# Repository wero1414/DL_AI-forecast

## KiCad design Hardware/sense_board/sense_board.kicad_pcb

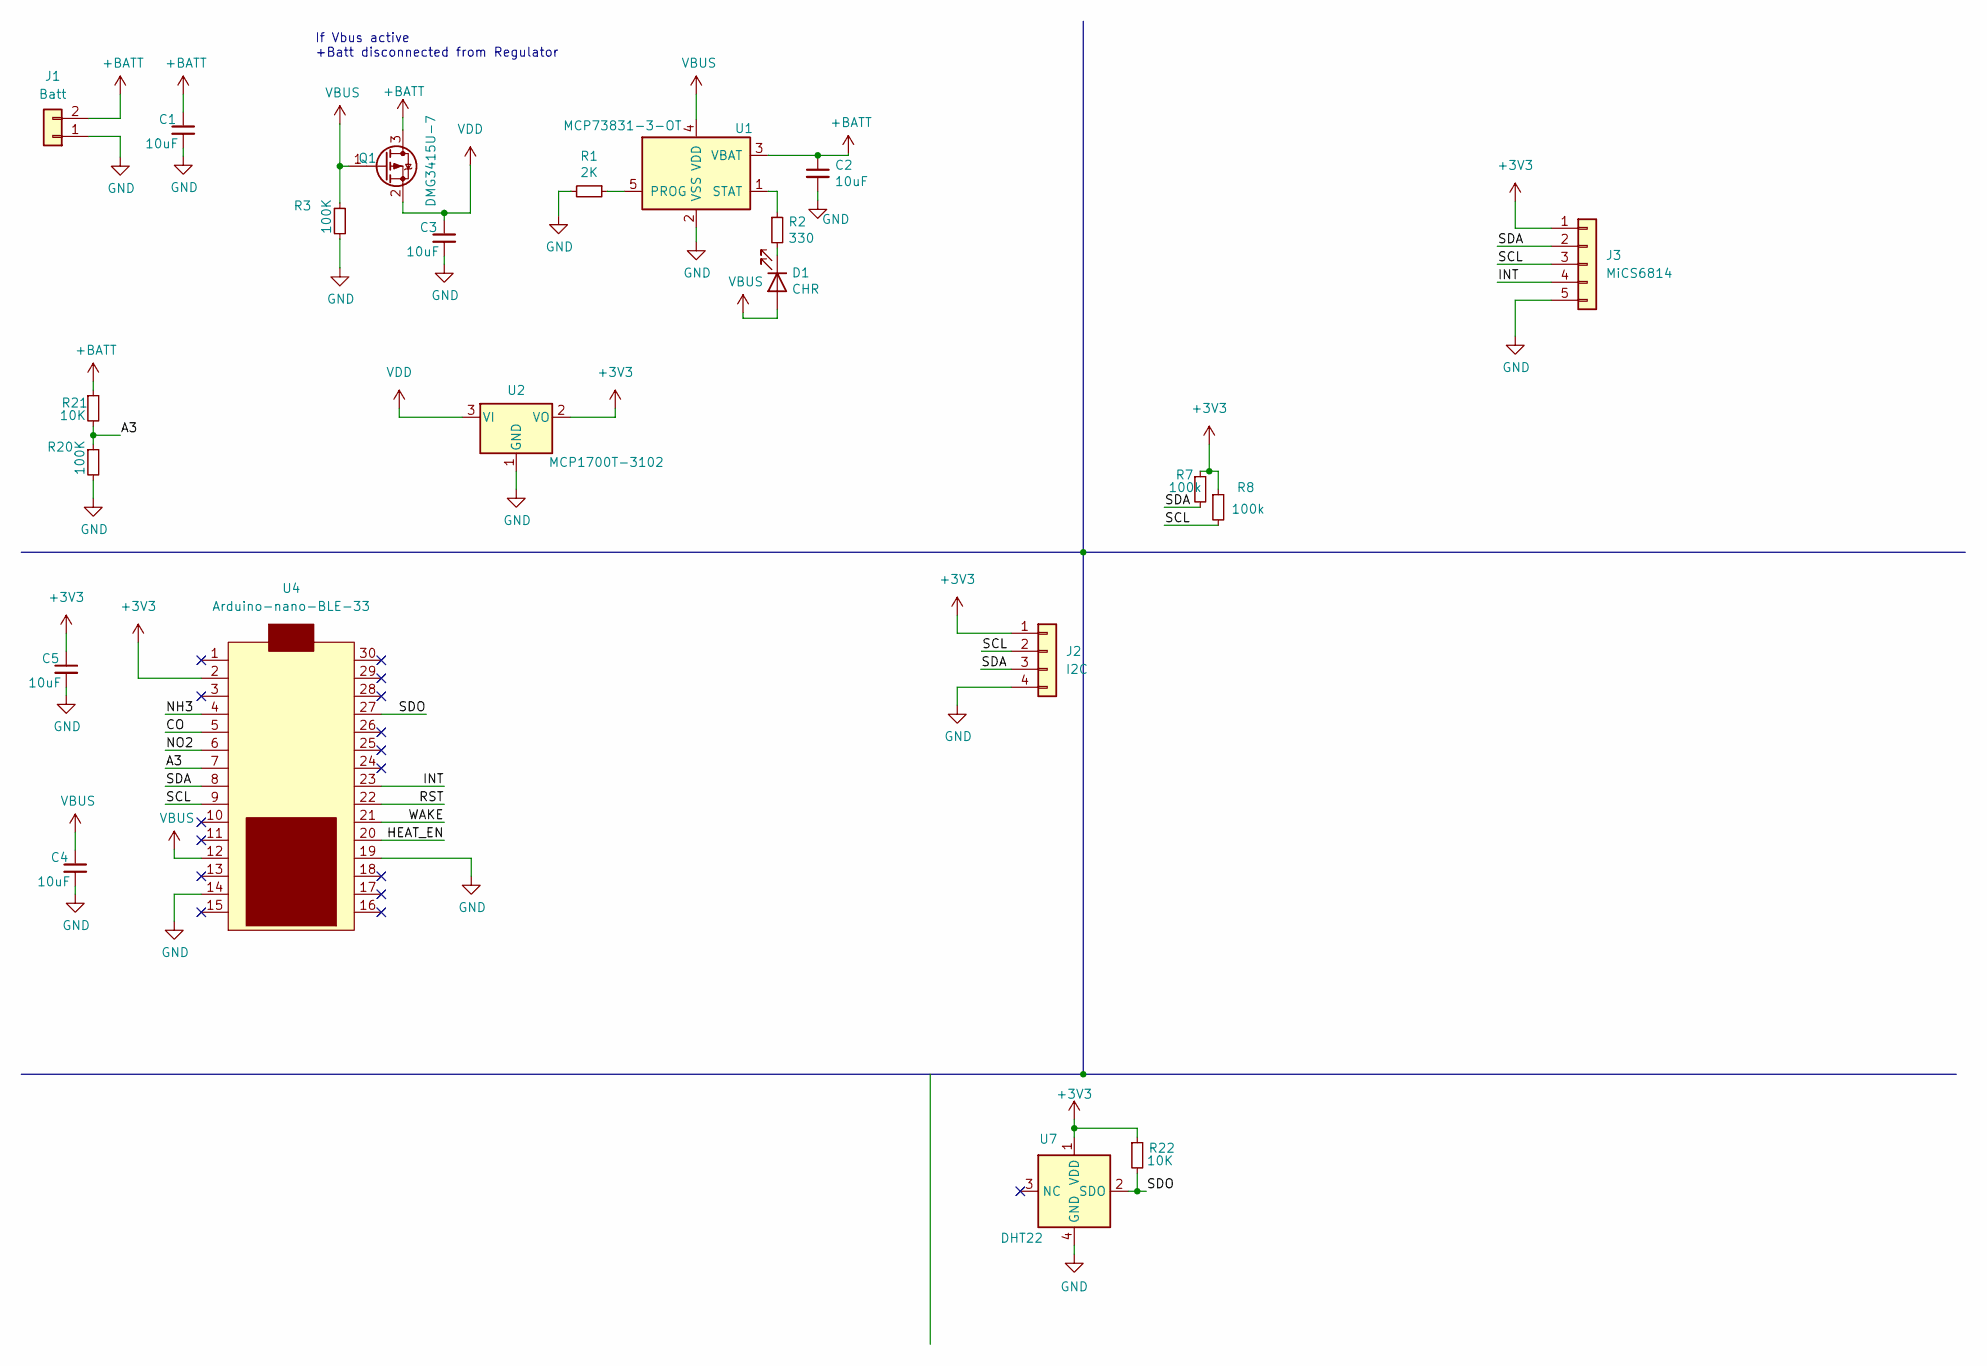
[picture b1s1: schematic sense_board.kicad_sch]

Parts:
C1, C2, C3, C4, C5: 10uF; C_0805_2012Metric
D1: CHR; LED_0805_2012Metric_Pad1.15x1.40mm_HandSolder
J1: Batt; JST_S2B-PH-SM4-TB(LF)(SN)
J2: I2C; PinHeader_1x04_P2.54mm_Vertical
J3: MiCS6814; PinHeader_1x05_P2.54mm_Vertical
Q1: DMG3415U-7; SOT-23
R1: 2K; R_0805_2012Metric
R2: 330; R_0805_2012Metric
R3, R20: 100K; R_0805_2012Metric
R7, R8: 100k; R_0805_2012Metric
R21, R22: 10K; R_0805_2012Metric
U1: MCP73831-3-OT; SOT-23-5
U2: MCP1700T-3102; SOT-23
U4: Arduino-nano-BLE-33; NANO_33_Footprint_SMD_Castell
U7: DHT22; ASAIR_AM2302_P2.54mm_Vertical

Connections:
+3V3: C5.1, J2.1, J3.1, R7.1, R8.1, R22.1, U2.2 (VO), U4.2, U7.1 (VDD)
+BATT: C1.1, C2.1, J1.2, Q1.3 (D), R21.1, U1.3 (VBAT)
/A3: R20.1, R21.2, U4.7
/CO: U4.5
/HEAT_EN: U4.20
/INT: J3.4, U4.23
/NH3: U4.4
/NO2: U4.6
/RST: U4.22
/SCL: J2.2, J3.3, R8.2, U4.9
/SDA: J2.3, J3.2, R7.2, U4.8
/SDO: R22.2, U4.27, U7.2 (SDO)
/WAKE: U4.21
GND: C1.2, C2.2, C3.2, C4.2, C5.2, J1.1, J2.4, J3.5, R1.2, R3.2, R20.2, U1.2 (VSS), U2.1 (GND), U4.14, U4.19, U7.4 (GND)
unnamed: D1.1 (K), R2.2
unnamed: R1.1, U1.5 (PROG)
unnamed: R2.1, U1.1 (STAT)
VBUS: C4.1, D1.2 (A), Q1.1 (G), R3.1, U1.4 (VDD), U4.12
VDD: C3.1, Q1.2 (S), U2.3 (VI)

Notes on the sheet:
If Vbus active +Batt disconnected from Regulator

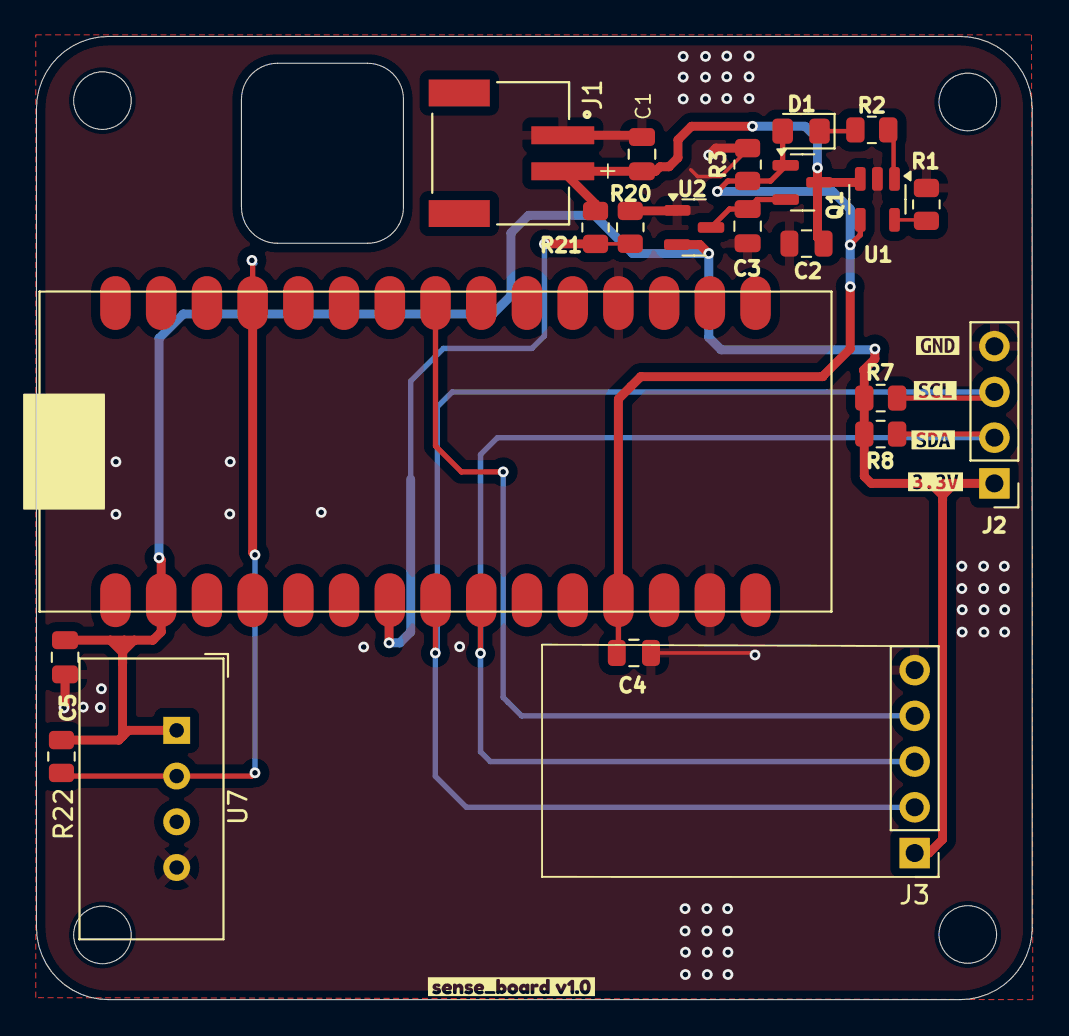
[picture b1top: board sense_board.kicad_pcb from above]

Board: 2 copper layers, 55.3 x 53.5 mm, 27 parts (0 on the bottom side), 13 nets.

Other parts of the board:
kibuzzard-67299F87: G***; kibuzzard-67299F87
kibuzzard-672967A3: G***; kibuzzard-672967A3
kibuzzard-672967AD: G***; kibuzzard-672967AD
kibuzzard-67296774: G***; kibuzzard-67296774
kibuzzard-67296794: G***; kibuzzard-67296794

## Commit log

2024-11-22 upload hardware
2024-11-22 upload python script to connect and retrieve data each 5 seconds
2024-11-22 upload firmware and libraries
